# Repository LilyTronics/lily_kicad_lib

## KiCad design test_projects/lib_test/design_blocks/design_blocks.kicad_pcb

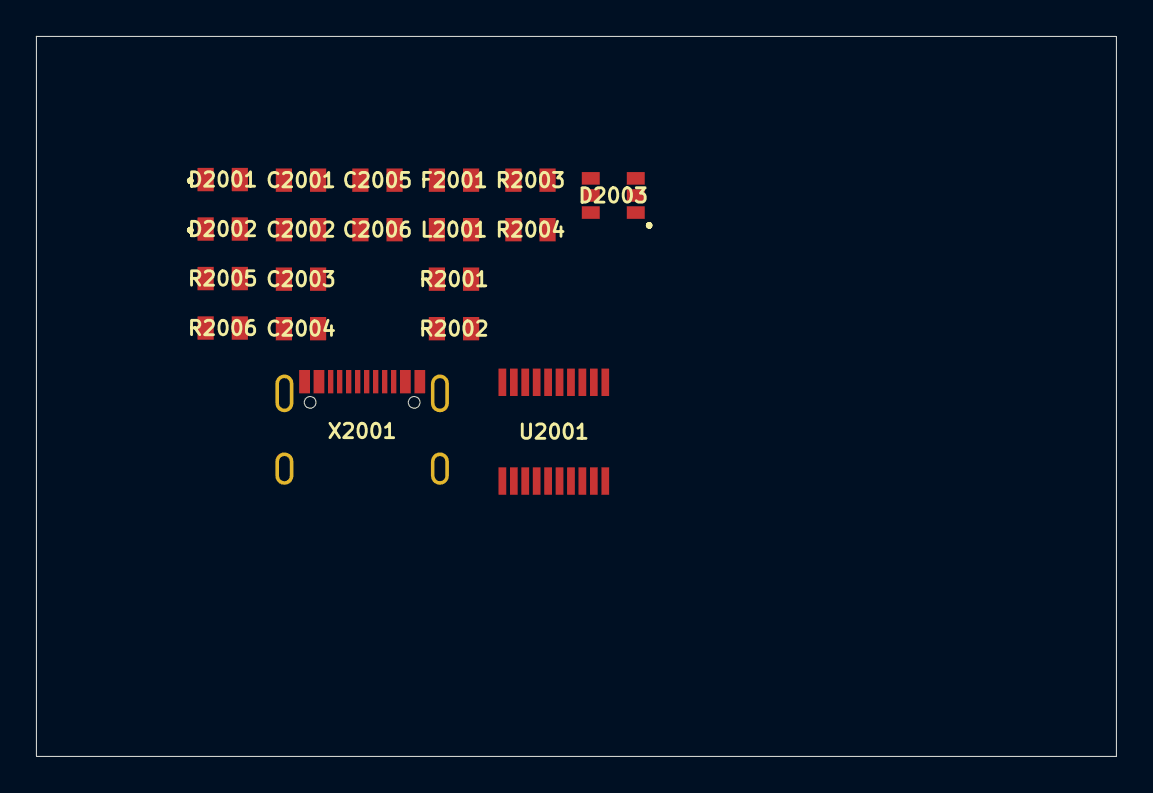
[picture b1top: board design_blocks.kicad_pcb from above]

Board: 2 copper layers, 60.0 x 40.0 mm, 19 parts (0 on the bottom side), 15 nets, no tracks yet.

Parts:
C2001: 10n; cap_0805
C2002, C2004: 100n; cap_0805
C2003: 4u7; cap_0805
C2005, C2006: 47p; cap_0805
D2001: RX; led_0805
D2002: TX; led_0805
D2003: SRV05-4; sot23-6_sc74
F2001: 0.35A/0.75A; fuse_ptc_0805
L2001: 600R/2A; ind_0805
R2001, R2002: 27R; res_0805
R2003, R2004: 5k1; res_0805
R2005, R2006: 470R; res_0805
U2001: FT231XS; ssop20_pitch25_341x154mil
X2001: usb_c; con_usb_c_receptacle_16p

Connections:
GND: C2001.2, C2002.2, C2003.2, C2004.2, C2005.2, C2006.2, D2003.2 (GND), R2003.2, R2004.2, U2001.6 (GND), U2001.16 (GND), X2001.1 (SH), X2001.A1 (GND), X2001.A12 (GND), X2001.B1 (GND), X2001.B12 (GND)
unnamed: C2004.1, D2001.2 (A), D2002.2 (A), U2001.3 (VCCIO), U2001.13 (3V3), U2001.14 (~RESET)
unnamed: D2001.1 (K), R2005.1
unnamed: D2002.1 (K), R2006.1
unnamed: C2006.1, D2003.1 (CH1), D2003.3 (CH2), R2002.2, X2001.A7 (D-), X2001.B7 (D-)
unnamed: C2005.1, D2003.4 (CH3), D2003.6 (CH4), R2001.2, X2001.A6 (D+), X2001.B6 (D+)
unnamed: C2001.1, D2003.5 (VCC), F2001.2, L2001.1
unnamed: F2001.1, X2001.A4 (VBUS), X2001.A9 (VBUS), X2001.B4 (VBUS), X2001.B9 (VBUS)
unnamed: R2005.2, U2001.17 (CBUS1)
unnamed: R2006.2, U2001.10 (CBUS2)
unnamed: R2001.1, U2001.11 (D+)
unnamed: R2002.1, U2001.12 (D-)
unnamed: C2002.1, C2003.1, L2001.2, U2001.15 (VCC)
unnamed: R2004.1, X2001.A5 (CC1)
unnamed: R2003.1, X2001.B5 (CC2)

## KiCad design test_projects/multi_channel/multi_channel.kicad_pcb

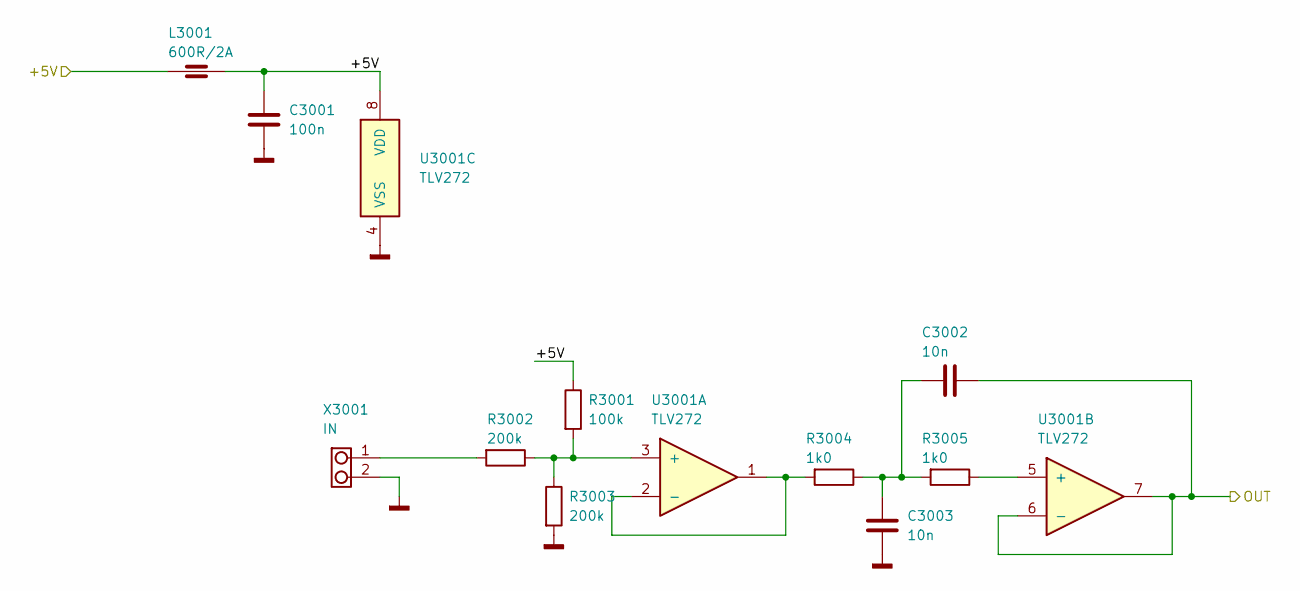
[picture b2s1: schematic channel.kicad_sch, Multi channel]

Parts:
C3001: 100n; cap_0805; JLCPCB_ID C49678
C3002, C3003: 10n; cap_0805; JLCPCB_ID C83170
L3001: 600R/2A; ind_0805; JLCPCB_ID C21519
R3001: 100k; res_0805; JLCPCB_ID C96346
R3002, R3003: 200k; res_0805; JLCPCB_ID C114562
R3004, R3005: 1k0; res_0805; JLCPCB_ID C95781
U3001: TLV272; soic8; JLCPCB_ID C398914
X3001: IN; con_jst_1x02_ph_2.00mm_right_angle_th; JLCPCB_ID C173752

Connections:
/Channel 1/+5V: C3001.1, L3001.1, L3001.2, R3001.1, U3001.8 (VDD); also elsewhere on the board
/Channel 1/OUT: C3002.1, U3001.6 (-), U3001.7; also elsewhere on the board
GND: C3001.2, C3003.2, R3003.2, U3001.4 (VSS), X3001.2; also elsewhere on the board
unnamed: C3002.2, C3003.1, R3004.1, R3005.2
unnamed: R3002.2, X3001.1
unnamed: R3001.2, R3002.1, R3003.1, U3001.3 (+)
unnamed: R3004.2, U3001.1, U3001.2 (-)
unnamed: R3005.1, U3001.5 (+)

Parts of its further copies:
C4001: 100n; cap_0805; JLCPCB_ID C49678
C4002, C4003: 10n; cap_0805; JLCPCB_ID C83170
L4001: 600R/2A; ind_0805; JLCPCB_ID C21519
R4001: 100k; res_0805; JLCPCB_ID C96346
R4002, R4003: 200k; res_0805; JLCPCB_ID C114562
R4004, R4005: 1k0; res_0805; JLCPCB_ID C95781
U4001: TLV272; soic8; JLCPCB_ID C398914
X4001: IN; con_jst_1x02_ph_2.00mm_right_angle_th; JLCPCB_ID C173752

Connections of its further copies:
/Channel 1/+5V: C4001.1, L4001.1, L4001.2, R4001.1, U4001.8 (VDD); also elsewhere on the board
/Channel 2/OUT: C4002.1, U4001.6 (-), U4001.7; also elsewhere on the board
GND: C4001.2, C4003.2, R4003.2, U4001.4 (VSS), X4001.2; also elsewhere on the board
unnamed: C4002.2, C4003.1, R4004.1, R4005.2
unnamed: R4002.2, X4001.1
unnamed: R4001.2, R4002.1, R4003.1, U4001.3 (+)
unnamed: R4004.2, U4001.1, U4001.2 (-)
unnamed: R4005.1, U4001.5 (+)

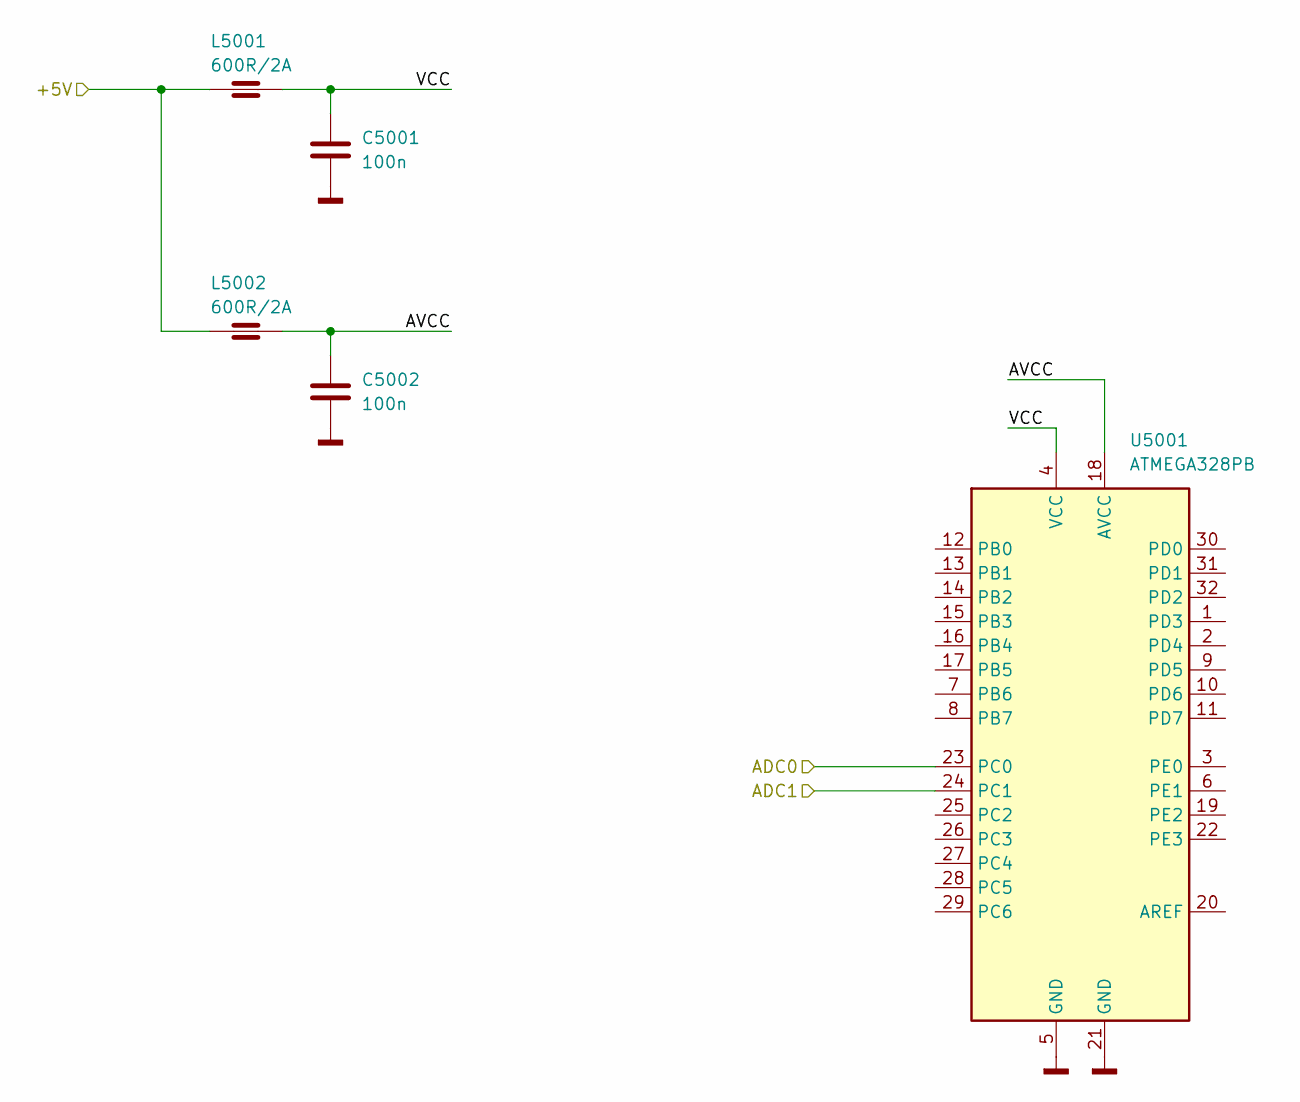
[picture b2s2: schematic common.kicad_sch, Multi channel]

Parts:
C5001, C5002: 100n; cap_0805; JLCPCB_ID C49678
L5001, L5002: 600R/2A; ind_0805; JLCPCB_ID C21519
U5001: ATMEGA328PB; tqfp32_pitch0.8_7x7mm; JLCPCB_ID C132230

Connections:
/Channel 1/+5V: L5001.1, L5002.1; also elsewhere on the board
/Channel 1/OUT: U5001.23 (PC0); also elsewhere on the board
/Channel 2/OUT: U5001.24 (PC1); also elsewhere on the board
/Common/AVCC: C5002.1, L5002.2, U5001.18 (AVCC)
/Common/VCC: C5001.1, L5001.2, U5001.4 (VCC)
GND: C5001.2, C5002.2, U5001.5 (GND), U5001.21 (GND); also elsewhere on the board

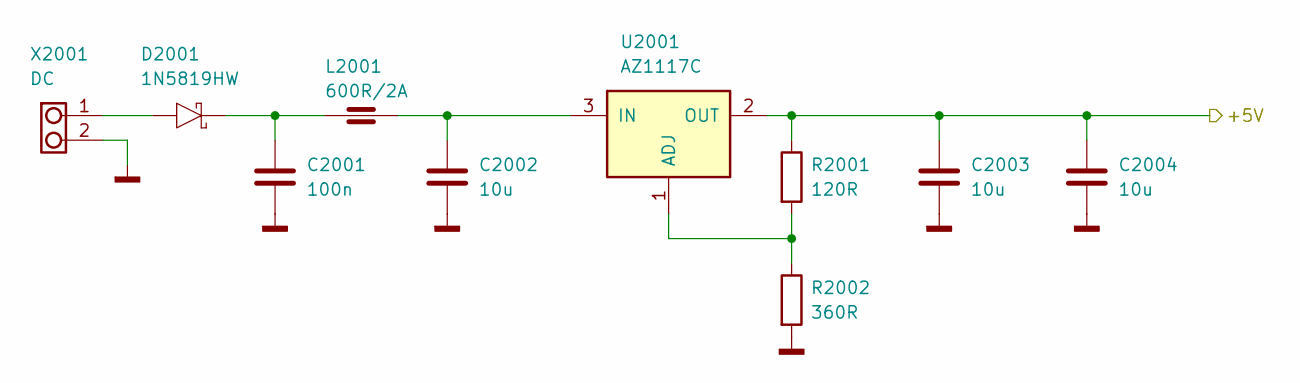
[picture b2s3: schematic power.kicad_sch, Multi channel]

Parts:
C2001: 100n; cap_0805; JLCPCB_ID C49678
C2002, C2003, C2004: 10u; cap_0805; JLCPCB_ID C15850
D2001: 1N5819HW; dio_sod123; JLCPCB_ID C82544
L2001: 600R/2A; ind_0805; JLCPCB_ID C21519
R2001: 120R; res_0805; JLCPCB_ID C114245
R2002: 360R; res_0805; JLCPCB_ID C137538
U2001: AZ1117C; sot223; JLCPCB_ID C95398
X2001: DC; con_jst_1x02_vh_3.96mm_right_angle_th; JLCPCB_ID C158007

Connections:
/Channel 1/+5V: C2003.1, C2004.1, R2001.1, U2001.2 (OUT); also elsewhere on the board
GND: C2001.2, C2002.2, C2003.2, C2004.2, R2002.2, X2001.2; also elsewhere on the board
unnamed: C2001.1, D2001.1, L2001.1
unnamed: D2001.2, X2001.1
unnamed: R2001.2, R2002.1, U2001.1 (ADJ)
unnamed: C2002.1, L2001.2, U2001.3 (IN)

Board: 2 copper layers, 37 parts (0 on the bottom side), 20 nets, no tracks yet.
